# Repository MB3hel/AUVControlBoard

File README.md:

# AUV Control Board

Motion controller for Autonomous Underwater Vehicles (AUVs) supporting motion in 6 degrees of freedom. Designed for vehicles with fixed position thrusters.

The Control Board is a coprocessor designed to assist a main computer (typically an embedded Linux computer) control the vehicle.

## Repository Structure

- `docs`: Documentation for users of the control board. This is a mkdocs project.
- `firmware`: PlatformIO project and source code for ControlBoard firmware.
- `iface`: Contains reference implementation to communicate with and use control board. Written in python.
- `pcb`: Contains PCB design files for v2.1
- `references`: Various links and pdfs providing information about components and libraries used on the control board. Intended for firmware developers.

## License
- The firmware (`firmware` directory) is licensed under the GNU General Public License version 3 or later (GPL-3.0-or-later). Note that third party code contained in the firmware directory (`firmware/thirdparty`) is **not** covered by this license. Third party code is distributed under the terms of the software's own license. License files are included for such third party software.
- The documentation (`docs` directory) is currently all rights reserved
- The interface scripts (`iface` directory) are licensed under the GNU General Public License version 3 or later (GPL-3.0-or-later).
- The reference information (`references`) is a collection of various resources from various sources. These are all publicly accessible (and downloadable) resources (at time of writing), but are not owned by or licensed by this project in any way. The license terms of these resources depend on the specific resource.

## View Documentation

[https://mb3hel.github.io/AUVControlBoard/](https://mb3hel.github.io/AUVControlBoard/)

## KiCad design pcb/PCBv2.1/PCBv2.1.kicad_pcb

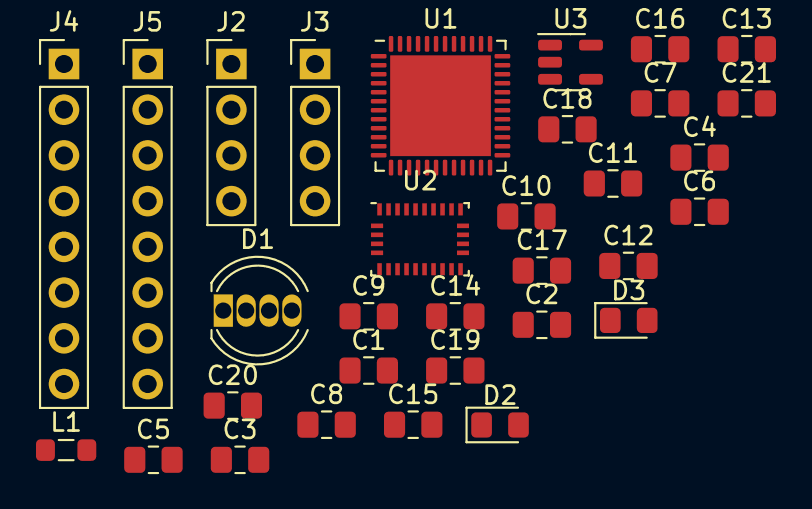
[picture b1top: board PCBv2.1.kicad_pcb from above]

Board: 2 copper layers, 32 parts (0 on the bottom side), 31 nets, no tracks yet.

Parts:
C1, C5, C13: 4.7u; C_0805_2012Metric_Pad1.18x1.45mm_HandSolder
C2, C4, C12, C21: 1u; C_0805_2012Metric_Pad1.18x1.45mm_HandSolder
C3, C7, C8, C9, C10, C11, C20: 100n; C_0805_2012Metric_Pad1.18x1.45mm_HandSolder
C6: 10u; C_0805_2012Metric_Pad1.18x1.45mm_HandSolder
C14, C15, C18, C19: 22p; C_0805_2012Metric_Pad1.18x1.45mm_HandSolder
C16, C17: 8p; C_0805_2012Metric_Pad1.18x1.45mm_HandSolder
D1: LED_RGBA; LED_D5.0mm-4_RGB
D2: Blue; LED_0805_2012Metric_Pad1.15x1.40mm_HandSolder
D3: Red; LED_0805_2012Metric_Pad1.15x1.40mm_HandSolder
J2, J3: Conn_01x04; PinHeader_1x04_P2.54mm_Vertical
J4, J5: Conn_01x08; PinHeader_1x08_P2.54mm_Vertical
L1: 1kOhm; L_0805_2012Metric_Pad1.05x1.20mm_HandSolder
U1: STM32F411CEUx; QFN-48-1EP_7x7mm_P0.5mm_EP5.6x5.6mm
U2: BNO055; LGA-28_5.2x3.8mm_P0.5mm
U3: AP2112K-3.3; SOT-23-5

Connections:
+3V3: C4.1, C5.1, C6.1, C7.1, C8.1, C9.1, C10.1, C20.1, D1.3 (A), J2.1, J3.4, L1.1, U1.1 (VBAT), U1.24 (VDD), U1.36 (VDD), U1.48 (VDD), U2.3 (VDD), U2.28 (VDDIO), U3.5 (VOUT)
+5V: C1.1, C2.1, U3.1 (VIN)
/BNO_INT: U1.25 (PB12), U2.14 (INT)
/BNO_RST: U1.26 (PB13), U2.11 (~RESET)
/NRST: C3.1, U1.7 (NRST)
/OSC32_IN: C18.1, U1.3 (PC14)
/OSC32_OUT: C19.1, U1.4 (PC15)
/OSC_IN: C16.1, U1.5 (PH0)
/OSC_OUT: C17.1, U1.6 (PH1)
/RGB_B: D1.2 (BK), U1.43 (PB7)
/RGB_G: D1.1 (GK), U1.42 (PB6)
/RGB_R: D1.4 (RK), U1.29 (PA8)
/SCL1: J2.3, U1.45 (PB8), U2.19 (COM1)
/SDA1: J2.4, U1.46 (PB9), U2.20 (COM0)
/SWCLK: J3.2, U1.37 (PA14)
/SWDIO: J3.3, U1.34 (PA13)
/SW_LED: D2.1 (K), U1.2 (PC13)
/THR1: J5.1, U1.19 (PB1)
/THR2: J5.2, U1.18 (PB0)
/THR3: J5.3, U1.17 (PA7)
/THR4: J5.4, U1.16 (PA6)
/THR5: J5.5, U1.13 (PA3)
/THR6: J5.6, U1.12 (PA2)
/THR7: J5.7, U1.11 (PA1)
/THR8: J5.8, U1.10 (PA0)
/VCAP1: C13.1, U1.22 (VCAP1)
/VDDA: C11.1, C12.1, L1.2, U1.9 (VDDA)
GND: C1.2, C2.2, C3.2, C4.2, C5.2, C6.2, C7.2, C8.2, C9.2, C10.2, C11.2, C12.2, C13.2, C14.2, C15.2, C16.2, C17.2, C18.2, C19.2, C20.2, C21.2, D3.1 (K), J2.2, J3.1, J4.1, J4.2, J4.3, J4.4, J4.5, J4.6, J4.7, J4.8, U1.8 (VSSA), U1.23 (VSS), U1.35 (VSS), U1.47 (VSS), U1.49 (VSS), U2.2 (GND), U2.5 (PS1), U2.6 (PS0), U2.15 (GNDIO), U2.16 (GNDIO), U2.18 (COM2), U2.25 (GNDIO), U3.2 (GND)
unnamed: C14.1, U2.26 (XOUT32)
unnamed: C15.1, U2.27 (XIN32)
unnamed: C21.1, U2.9 (CAP)

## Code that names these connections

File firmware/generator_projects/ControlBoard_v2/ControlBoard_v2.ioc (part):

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Mcu.Name=STM32F411C(C-E)Ux
Mcu.Package=UFQFPN48
Mcu.UserName=STM32F411CEUx
PA0-WKUP.GPIOParameters=GPIO_Label
PA0-WKUP.GPIO_Label=THR8
PA0-WKUP.Signal=S_TIM5_CH1
PA1.GPIOParameters=GPIO_Label
PA1.GPIO_Label=THR7
PA1.Signal=S_TIM5_CH2
PA10.Mode=OTG/Dual_Role_Device
PA10.Signal=USB_OTG_FS_ID
PA11.Mode=OTG/Dual_Role_Device
PA11.Signal=USB_OTG_FS_DM
PA12.Mode=OTG/Dual_Role_Device
PA12.Signal=USB_OTG_FS_DP
PA2.GPIOParameters=GPIO_Label
PA2.GPIO_Label=THR6
PA2.Signal=S_TIM5_CH3
PA3.GPIOParameters=GPIO_Label
PA3.GPIO_Label=THR5
PA3.Signal=S_TIM5_CH4
PA6.GPIOParameters=GPIO_Label
PA6.GPIO_Label=THR4
PA6.Signal=S_TIM3_CH1
PA7.GPIOParameters=GPIO_Label
PA7.GPIO_Label=THR3
PA7.Signal=S_TIM3_CH2
PA8.GPIOParameters=GPIO_Label
PA8.GPIO_Label=RGBLED_R
PA8.Signal=S_TIM1_CH1
PA9.Mode=Activate_VBUS
PA9.Signal=USB_OTG_FS_VBUS
PB0.GPIOParameters=GPIO_Label
PB0.GPIO_Label=THR2
PB0.Signal=S_TIM3_CH3
PB1.GPIOParameters=GPIO_Label
PB1.GPIO_Label=THR1
PB1.Signal=S_TIM3_CH4
PB6.GPIOParameters=GPIO_Label
PB6.GPIO_Label=RGBLED_G
PB6.Signal=S_TIM4_CH1
PB7.GPIOParameters=GPIO_Label
PB7.GPIO_Label=RGBLED_B
PB7.Signal=S_TIM4_CH2
PB8.Mode=I2C
PB8.Signal=I2C1_SCL
PB9.Mode=I2C
PB9.Signal=I2C1_SDA
PC13-ANTI_TAMP.GPIOParameters=GPIO_Label
PC13-ANTI_TAMP.GPIO_Label=BLUE_LED
PC13-ANTI_TAMP.Signal=GPIO_Output
PC14-OSC32_IN.Mode=LSE-External-Oscillator
PC14-OSC32_IN.Signal=RCC_OSC32_IN
PC15-OSC32_OUT.Mode=LSE-External-Oscillator
PC15-OSC32_OUT.Signal=RCC_OSC32_OUT
PH0\ -\ OSC_IN.Mode=HSE-External-Oscillator
PH0\ -\ OSC_IN.Signal=RCC_OSC_IN
PH1\ -\ OSC_OUT.Mode=HSE-External-Oscillator
PH1\ -\ OSC_OUT.Signal=RCC_OSC_OUT
RCC.HSE_VALUE=25000000
RCC.SYSCLKFreq_VALUE=96000000
RCC.SYSCLKSource=RCC_SYSCLKSOURCE_PLLCLK
board=custom

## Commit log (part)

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2023-04-01 Implement v2 wdog check
2023-04-01 Fix v1 reset command showing as wdt reset cause
2023-04-01 Document reset cause query
2023-04-01 Deployed acc465c with MkDocs version: 1.4.2
2023-04-03 Fix unit inconsistency in sassist math
2023-04-03 Update docs info on sassist mode
2023-04-07 Fix lots of conversions
2023-04-07 More script fixes
2023-04-08 Fix quat to grav vector sign error
2023-04-08 Add 'empty' folders
2023-04-08 Finished pcb schematic
2023-04-08 Labeled all pins in pcb schematic
2023-04-08 Added initial pcb work
2023-04-08 Add headers to pcb schematic
2023-04-08 Add footprints for resistors
2023-04-08 Add specific USB-C connector and resistor part numbers to pcb schematic
2023-04-08 Add button part numbers for pcb
2023-04-09 Created packaging script
2023-04-09 Add docs to packages
2023-04-10 Add simulator hijack command
2023-04-11 Limit message ids from pc
2023-04-11 Add more simulation globals
2023-04-11 Add selection logic for simulator sensors
2023-04-11 Document simhijack command
2023-04-11 Remove pointless comments
2023-04-11 Implement SIMDAT command
2023-04-11 Adapt to new cmd interface for simulator
2023-04-15 Remove direct sensor data from sim
2023-04-15 SIMHIJACK changes trigger motors to stop
2023-04-16 Sensors use simulator data when hijacked by simulator
2023-04-16 Provides motor speeds to simulator
2023-04-16 Motor watchdog works in simulation
2023-04-16 Sim mode uses raw speeds
2023-04-16 Fix simstat message length
2023-04-16 Remove more sim restrictions
2023-04-16 Fix sensors not ready in sim hijack
2023-04-17 Revert "Stability assist fixes???"
    This reverts commit f89ec4bd9c165aacd3eb252ae246a81853326f84.
2023-04-17 Fix sassist divide by zero error
2023-04-17 launch doesn't reset simulator on connect
2023-04-17 Fix wrong diff quat calculatoin in sassist
2023-04-17 More sassist experiments
2023-04-18 Remove numeric instability issue in sassist quat to axis angle
2023-04-18 remove angular momentum transform of basis from ssassist
2023-04-18 iface script uses sassist2
2023-04-18 Use quaternion negation to handle direction of rotation in sassist
2023-04-19 partial fix for sassist1 (tracks yaw properly)
2023-04-20 Remove pointless nop
2023-04-20 Rename parameters in motor control speed set functions (firmware)
2023-04-22 Rename pid objects
2023-04-22 Fix comments and var names in cmdctrl
2023-04-22 Update scripts calling tune commands
2023-04-22 Initial attempts to fix global rotation
2023-04-22 More global mode debug work
2023-04-30 Global chooses euler by min roll
2023-04-30 Add reldof command
2023-04-30 Implement global mode relative scale down
2023-05-05 Document reldof set command
2023-05-11 Rename some interface scripts
2023-05-11 Cleanup some motor control code and comments in code
2023-05-11 Global mode rotation fixes
    - Implemented speed up-scaling
    - Fixed pitch math issue
    - Added comments about gimbal lock issue with GLOBAL mode
2023-05-11 Revert "First attempt at global mode pitch motion hysteresis"
    This reverts commit 64ae44dc6fb54b71ff886c90b4ec1dd7b130ce75.
2023-05-11 Better comments for gimbal lock in global mode
2023-05-11 Validate reldof values in firmware cmdctrl
2023-05-11 Cleanup upscaling code
2023-05-11 Added reldof scaling to global mode translation
2023-05-12 Default timeout in inface longer for simulator
2023-05-12 Improve vehicle definitions
    - Add PID tuning to vehicles
    - Different instances for sim and real vehicles
2023-05-12 Actually tune depth in iface vehicle
2023-05-12 Implement reldof scaling in sassist mode
2023-05-12 Move PID tune functions in motor_control.c
2023-05-12 Cleanup sassist code using functions made for global code
2023-05-12 Cleanup simulated sensor data flow (slightly)
2023-05-13 Move interface scritps
2023-05-13 Add user vehicles file support to iface
2023-05-13 Add user vehicles template
2023-05-13 Update iface header comments
2023-05-13 Add depth hold mode example script
2023-05-13 Implement LDHOLD in firmware
2023-05-13 Revert "Implement LDHOLD in firmware"
    This reverts commit 691a80f09e8bd965676daa2cb92e33c950973930.
    Reverted as this control mode is just a VERY bad idea!
2023-05-13 PID reset check uses a tolerence
2023-05-13 Add dev with simulator info to docs
2023-05-13 Deployed bf9b44c with MkDocs version: 1.4.2
2023-05-13 Start math docs rewrite
2023-05-13 Add DoF matrix to math docs
2023-05-13 Start to work on global mode math docs
2023-05-13 Update docs layout
2023-05-22 Partial global mode math docs
2023-05-22 Add global mode gif to math page
2023-05-22 Added sassist math to docs
2023-05-22 Remove some todos from math docs
2023-05-22 Remove old math page from docs
2023-05-22 Deployed 4d0614a with MkDocs version: 1.4.2
2023-05-22 Deployed aa17373 with MkDocs version: 1.4.2
2023-05-24 PID reset condition based on user inputs not target quat
2023-06-08 Fix interface scripts on windows
2023-06-08 Fix incorrect simstat message under simulator hijack
2023-06-08 Fix unit issue in fallback euler sassist
2023-06-10 Fix vehicle iface on older python
2023-06-11 Cleanup of gamepad examples
2023-06-11 Improve depth control with gamepad sassist
2023-06-11 Add drive station link for gamepad iface scripts
2023-06-11 Fix package script
2023-06-15 Fix potential divide by zero for reldof
2023-06-15 Remove fallback sassist
2023-06-15 Fix angle pid reset logic
2023-06-15 sensordata script shows accum angles
2023-06-18 Outline eeprom header
2023-06-20 Partial smarteeprom implementation for v1
2023-06-20 Cleanup some v1 eeprom comments
2023-06-20 Comment spelling fixes
2023-06-20 Implement v1 SmartEEPROM fuse settings
2023-06-20 Add calibration signature using eeprom
2023-06-21 Initial work on STM32 eeprom emulation
2023-06-21 v2 flash via stm32-dfu fixed with eeprom
2023-06-26 Implement v2 emulated eeprom
2023-06-26 Switch emulated eeprom to use 16-bit values
2023-06-26 Outline calibration data and load / store
2023-06-26 Start work on calibration related commands
2023-06-27 Wrote guided calibration script logic
2023-06-28 Reading of BNO055 calibration now occurs in config mode
2023-06-28 Clarify calibration values
2023-06-28 Fix bno055 calibration constants saved to wrong eeprom addresses
2023-06-28 Implement apply calibration on startup of bno055
2023-06-28 Fix BNO055 i2c race condition
2023-06-28 Fix various issues with v2 eeprom emulation
2023-06-28 Note another eeprom emulation function modification for v2
2023-06-28 Added manual calibration procedure to BNO055 calibrate script
2023-06-28 Add uint info to raw imu data script
2023-06-29 Add bno055 calibration script instructions
2023-06-29 Reconfiguration of BNO055 preserves axis configuration
2023-06-29 Add axis config calibration note to docs
2023-06-29 Make depth sensor calibration non-persistent
2023-06-29 Remove unused calibration macros
2023-06-29 Convert ms5837 pressure units to Pa
2023-06-29 Document pressure read from MS5837
2023-06-29 MS5837 temperature data is provided
2023-06-29 Document MS5837 calibration commands
2023-06-29 Add MS5837 calibration to docs
2023-07-10 Clarify BNO055 calibartion procedure in docs
2023-07-10 Document BNO055 reset command
2023-07-12 Add bootloader update warnings to docs
2023-07-22 Improve gamepad sassist depth control
2023-08-22 Start outlining local nav and local depth hold modes
2023-08-24 Add support for simulator set / get vehicle commands
2023-08-28 Add another vehicle
2023-09-18 Fix initial depth issues with gamepad sassist
2023-09-18 Add ohold functions to iface script
2023-09-18 Create ohold example scripts
2023-09-18 Add printed enable / disable warning to gamepad script
2023-09-18 Fix typo in printed message (gamepad iface script)
2023-09-24 Add correct (pink) OHOLD led color
2023-09-24 Fix OHOLD2 argument parsing
2023-09-24 Update math docs to explain OHOLD mode
2023-09-24 Change PID tune function names in iface script
2023-09-24 Implement version query in firmware
2023-09-24 Add version query to messages docs
2023-09-24 Add version to interface script
2023-09-25 Initial work for versioning
2023-09-25 Update versions
2023-09-25 Fix iface version string
2023-09-25 Update ohold scripts
2023-09-29 Fix SASSIST commands in docs
2023-09-30 Add local speed set zero to launch script
2023-10-01 Increase time after BNO055A command to prevent "zero data" from IMU
2023-10-01 Add version check notes to user guide
2023-10-01 Deployed fd2cfda with MkDocs version: 1.3.0
2023-10-03 Initial work on adding Linux compatability
2023-10-03 Restore v2 build functionality
2023-10-03 Move sim variables to cmdctrl
2023-10-04 More code cleanup / reorganization
2023-10-05 MS5837 uses new i2c mutex method
2023-10-05 Cleanup IMU code
2023-10-05 Update depth sensor task in app
2023-10-05 Reorganize init code in main
2023-10-06 Adapt motor control code to use struct targets
2023-10-06 Change BNO055 and MS5837 data commands to IMU and DEPTH commands
2023-10-06 Finished cleaning up command parsing in firmware
2023-10-06 Implement usb abstraction
2023-10-06 Add notifications back to firmware app.c
2023-10-06 Update iface to use new command names
2023-10-07 Revert to individual sensor mutexes
2023-10-07 Fix sensor parsing with new messages in iface
2023-10-07 Cleanup / fixes to iface scripts
2023-10-14 Fix ms5837 calibration
2023-10-27 Base work for thruster PWM parameters
2023-10-27 Support tpwm in iface
2023-10-27 Fix PWM period for thrusters
2023-10-27 Add TPWM to docs
2023-10-28 Fix DoF matrix clobbering and calls in gamepad iface script
2023-10-28 Add CONTROL_BOARD_SIM define for all sim configs
2023-10-28 Initial simcb USB implementation
2023-10-28 Add dummy hardware implementation for simcb
2023-10-28 Add debug config for simcb linux
2023-10-29 Implement USB comms over stdio for simcb linux
2023-10-30 Some (not quite right) progress on TCP for SimCB usb
2023-10-30 Baseline work and comments for a proper method of using sockets for simcb usb
2023-11-01 Seemingly functional usb socket for simcb linux
2023-11-01 Remove debug usb socket loopback
2023-11-01 Fix socket disconnect detection
2023-11-01 Clarify heartbeat message
2023-11-01 Enable heartbeat for all CB
2023-11-01 Update debug launch for macos simcb
2023-11-01 Convert sock calls to winsock for simcb win (no threads yet)
2023-11-01 Implement dealy api for simcb windows
2023-11-01 Fix some usb implementation bugs for both win and posix simcb
2023-11-02 Update launch json to run in executable directory
2023-11-02 Some more doc restructuring
2023-11-02 Some updates to dev docs
2023-11-02 Move arp gamepad stuff into gamepad example
2023-11-02 Fix file name in docs
2023-11-02 Initial work on new pack script
2023-11-02 Add port number checking
2023-11-02 Add print and exit for simcb debug halt
2023-11-02 Initial work on cmd script
2023-11-03 SimCB debug halt waits on exit if interactive
2023-11-03 Remove test crash from firmware
2023-11-03 Fix simcb windows build
2023-11-03 Fix windows simcb package
2023-11-03 Update simcb pack scripts
2023-11-03 Initial GH actions workflow
2023-11-03 Different trigger for action
2023-11-03 Fix base package deps
2023-11-03 Run workflow apt-get as root
2023-11-03 Don't link pthread for bare metal firmware
2023-11-03 Install deps before building docs
2023-11-03 Fix simcb linux working directory in workflow
2023-11-03 Check mac build
2023-11-03 Don't use realpath on macos
2023-11-03 No need for macos command
2023-11-03 Add simcb windows build to workflow
2023-11-03 Fix workflow syntax
2023-11-03 Fix job ids
2023-11-03 Fix combine stage of workflow
2023-11-03 Change action trigger to manual dispatch
2023-11-03 Add workflow from feature/simcb
2023-11-03 Implement sim wdt for windows
2023-11-03 Add tcp connect option to iface for simcb
2023-11-03 iface supports simulator with different ports
2023-11-15 Update version
2023-11-15 Revise and cleanup existing sections of math docs
2023-11-15 IMU angles are reset when bno055 axis config changes
2023-11-15 Add accumulated euler angles to math docs
2023-11-15 Improve outline of other derivations
2023-11-25 Prevent deadlock (and watchdog reset) if nan does make it to motor control code
2023-11-25 cmdctrl corrects nan inputs to zero
2024-01-26 Bump version
2024-01-26 Remove redundant sections from math docs
2024-05-05 Various docs additions
2024-05-05 Organize message docs to match structure of firmware parser
2024-05-05 Add note about INVALID_CMD acks when sensor is not active
